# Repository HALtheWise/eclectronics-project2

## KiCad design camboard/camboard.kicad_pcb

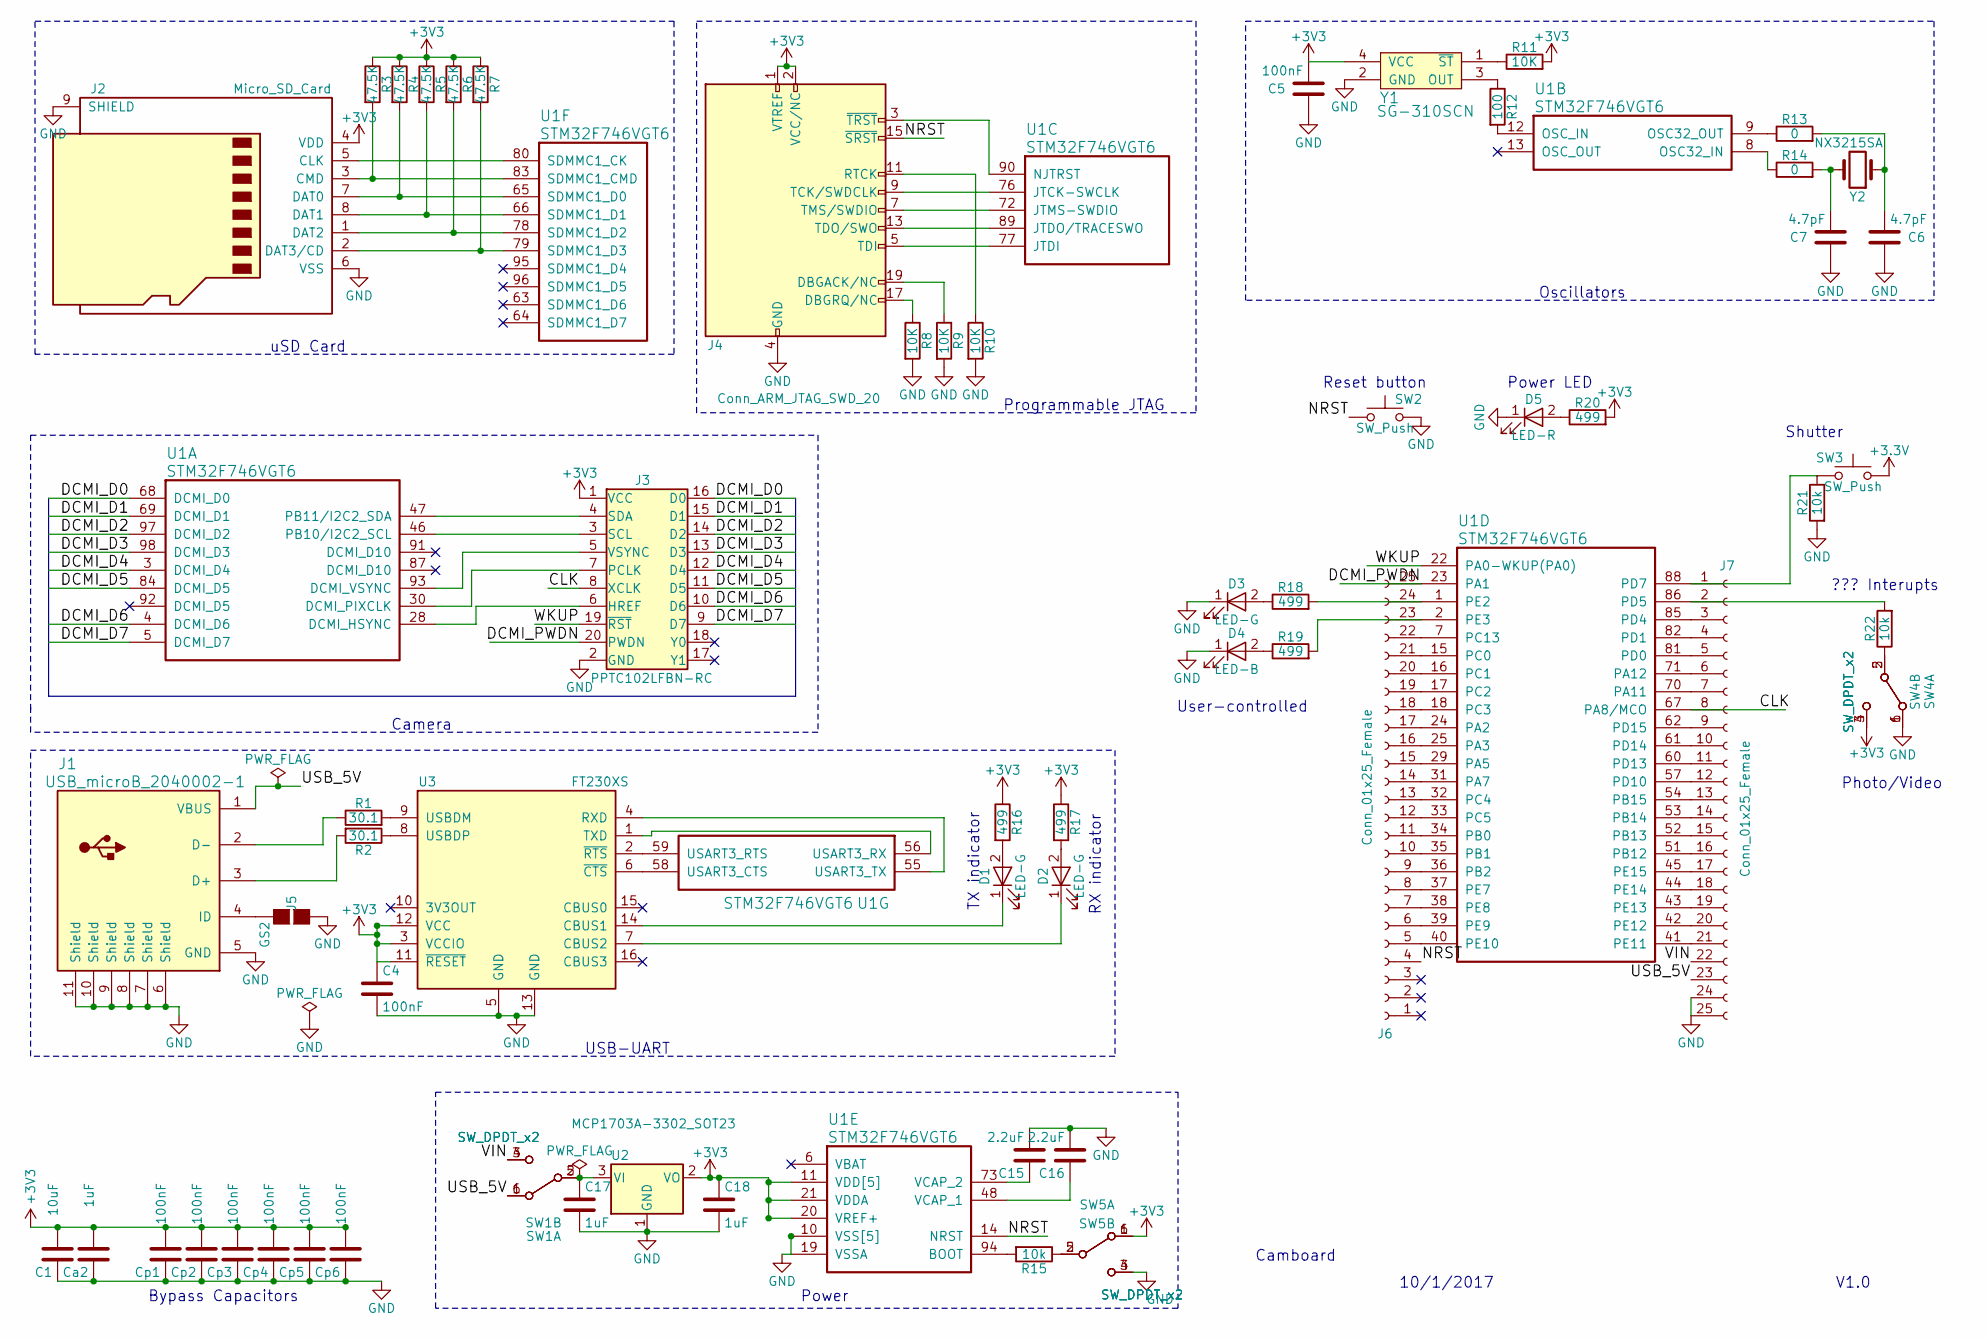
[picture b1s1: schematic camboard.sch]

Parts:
C1: 10uF; C_0805
C4, C5: 100nF; C_0603
C6, C7: 4.7pF; C_0603
C15, C16: 2.2uF; C_0805
C17, C18: 1uF; C_0603
Ca2: 1uF; C_0603
Cp1, Cp2, Cp3, Cp4, Cp5, Cp6: 100nF; C_0603
D1, D2, D3: LED-G; LED_0805
D4: LED-B; LED_0805
D5: LED-R; LED_0805
J1: USB_microB_2040002-1; USB_microB_2040002-1_alt
J2: Micro_SD_Card; 114-00841-68
J3: PPTC102LFBN-RC; Socket_Strip_Straight_2x10_Pitch2.54mm
J4: Conn_ARM_JTAG_SWD_20; Socket_Strip_Straight_2x10_Pitch2.54mm
J5: GS2
J6, J7: Conn_01x25_Female; Socket_Strip_Straight_1x25_Pitch2.54mm
R1, R2: 30.1; R_0603
R3, R4, R5, R6, R7: 47.5K; R_0603
R8, R9, R10, R11: 10K; R_0603
R12: 100; R_0603
R13, R14: 0; R_0603
R15, R21, R22: 10k; R_0603
R16, R17, R18, R19, R20: 499; R_0603
SW1, SW4, SW5: SW_DPDT_x2; JS202011SCQN
SW2, SW3: SW_Push; SW_SPST_B3U-1000P
U1: STM32F746VGT6; LQFP-100_14x14mm_Pitch0.5mm
U2: MCP1703A-3302_SOT23; SOT-23
U3: FT230XS; SSOP-16_3.9x4.9mm_Pitch0.635mm
Y1: SG-310SCN; Crystal_SMD_3225-4pin_3.2x2.5mm
Y2: NX3215SA; Crystal_SMD_3215-2pin_3.2x1.5mm

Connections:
/CLK: J3.8 (XCLK), J7.8, U1.67 (PA8/MCO)
/DCMI_D0: J3.16 (D0), U1.68 (DCMI_D0)
/DCMI_D1: J3.15 (D1), U1.69 (DCMI_D1)
/DCMI_D2: J3.14 (D2), U1.97 (DCMI_D2)
/DCMI_D3: J3.13 (D3), U1.98 (DCMI_D3)
/DCMI_D4: J3.12 (D4), U1.3 (DCMI_D4)
/DCMI_D5: J3.11 (D5), U1.84 (DCMI_D5)
/DCMI_D6: J3.10 (D6), U1.4 (DCMI_D6)
/DCMI_D7: J3.9 (D7), U1.5 (DCMI_D7)
/DCMI_PWDN: J3.20 (PWDN), J6.25, U1.23 (PA1)
/NRST: J4.15 (~SRST~), J6.4, SW2.1, U1.14 (NRST)
/USB_5V: J1.1 (VBUS), J7.23, SW1.1 (A), SW1.6 (A)
/VIN: J7.22, SW1.3 (C), SW1.4 (C)
/WKUP: J3.19 (~RST), U1.22 (PA0-WKUP(PA0))
GND: C1.1, C4.2, C5.1, C6.2, C7.1, C15.2, C16.2, C17.2, C18.2, Ca2.1, Cp1.1, Cp2.1, Cp3.1, Cp4.1, Cp5.1, Cp6.1, D3.1 (K), D4.1 (K), D5.1 (K), J1.5 (GND), J1.6 (Shield), J1.7 (Shield), J1.8 (Shield), J1.9 (Shield), J1.10 (Shield), J1.11 (Shield), J2.6 (VSS), J2.9 (SHIELD), J3.2 (GND), J4.4 (GND), J4.6 (GND), J4.8 (GND), J4.10 (GND), J4.12 (GND), J4.14 (GND), J4.16 (GND), J4.18 (GND), J4.20 (GND), J5.1 (G1), J7.24, J7.25, R8.2, R9.2, R10.2, R21.2, SW2.2, SW4.1 (A), SW4.6 (A), SW5.3 (C), SW5.4 (C), U1.10 (VSS[5]), U1.19 (VSSA), U1.26 (VSS[5]), U1.49 (VSS[5]), U1.74 (VSS[5]), U1.99 (VSS[5]), U2.1 (GND), U3.5 (GND), U3.13 (GND), Y1.2 (GND)
unnamed: C6.1, R13.2, Y2.1
unnamed: C7.2, R14.2, Y2.2
unnamed: C15.1, U1.73 (VCAP_2)
unnamed: C16.1, U1.48 (VCAP_1)
unnamed: C17.1, SW1.2 (B), SW1.5 (B), U2.3 (VI)
unnamed: D1.1 (K), U3.14 (CBUS1)
unnamed: D1.2 (A), R16.2
unnamed: D2.1 (K), U3.7 (CBUS2)
unnamed: D2.2 (A), R17.2
unnamed: D3.2 (A), R18.1
unnamed: D4.2 (A), R19.1
unnamed: D5.2 (A), R20.1
unnamed: J1.2 (D-), R1.1
unnamed: J1.3 (D+), R2.2
unnamed: J1.4 (ID), J5.2 (G2)
unnamed: J2.1 (DAT2), R6.2, U1.78 (SDMMC1_D2)
unnamed: J2.2 (DAT3/CD), R7.2, U1.79 (SDMMC1_D3)
unnamed: J2.3 (CMD), R3.2, U1.83 (SDMMC1_CMD)
unnamed: J2.5 (CLK), U1.80 (SDMMC1_CK)
unnamed: J2.7 (DAT0), R4.2, U1.65 (SDMMC1_D0)
unnamed: J2.8 (DAT1), R5.2, U1.66 (SDMMC1_D1)
unnamed: J3.3 (SCL), U1.46 (PB10/I2C2_SCL)
unnamed: J3.4 (SDA), U1.47 (PB11/I2C2_SDA)
unnamed: J3.5 (VSYNC), U1.93 (DCMI_VSYNC)
unnamed: J3.6 (HREF), U1.28 (DCMI_HSYNC)
unnamed: J3.7 (PCLK), U1.30 (DCMI_PIXCLK)
unnamed: J4.3 (~TRST~), U1.90 (NJTRST)
unnamed: J4.5 (TDI), U1.77 (JTDI)
unnamed: J4.7 (TMS/SWDIO), U1.72 (JTMS-SWDIO)
unnamed: J4.9 (TCK/SWDCLK), U1.76 (JTCK-SWCLK)
unnamed: J4.11 (RTCK), R10.1
unnamed: J4.13 (TDO/SWO), U1.89 (JTDO/TRACESWO)
unnamed: J4.17 (DBGRQ/NC), R8.1
unnamed: J4.19 (DBGACK/NC), R9.1
unnamed: J6.5, U1.40 (PE10)
unnamed: J6.6, U1.39 (PE9)
unnamed: J6.7, U1.38 (PE8)
unnamed: J6.8, U1.37 (PE7)
unnamed: J6.9, U1.36 (PB2)
unnamed: J6.10, U1.35 (PB1)
unnamed: J6.11, U1.34 (PB0)
unnamed: J6.12, U1.33 (PC5)
unnamed: J6.13, U1.32 (PC4)
unnamed: J6.14, U1.31 (PA7)
unnamed: J6.15, U1.29 (PA5)
unnamed: J6.16, U1.25 (PA3)
unnamed: J6.17, U1.24 (PA2)
unnamed: J6.18, U1.18 (PC3)
unnamed: J6.19, U1.17 (PC2)
unnamed: J6.20, U1.16 (PC1)
unnamed: J6.21, U1.15 (PC0)
unnamed: J6.22, U1.7 (PC13)
unnamed: J6.23, R19.2, U1.2 (PE3)
unnamed: J6.24, R18.2, U1.1 (PE2)
unnamed: J7.1, R21.1, SW3.2, U1.88 (PD7)
unnamed: J7.2, R22.2, U1.86 (PD5)
unnamed: J7.3, U1.85 (PD4)
unnamed: J7.4, U1.82 (PD1)
unnamed: J7.5, U1.81 (PD0)
unnamed: J7.6, U1.71 (PA12)
unnamed: J7.7, U1.70 (PA11)
unnamed: J7.9, U1.62 (PD15)
unnamed: J7.10, U1.61 (PD14)
unnamed: J7.11, U1.60 (PD13)
unnamed: J7.12, U1.57 (PD10)
unnamed: J7.13, U1.54 (PB15)
unnamed: J7.14, U1.53 (PB14)
unnamed: J7.15, U1.52 (PB13)
unnamed: J7.16, U1.51 (PB12)
unnamed: J7.17, U1.45 (PE15)
unnamed: J7.18, U1.44 (PE14)
unnamed: J7.19, U1.43 (PE13)
unnamed: J7.20, U1.42 (PE12)
unnamed: J7.21, U1.41 (PE11)
unnamed: R1.2, U3.9 (USBDM)
unnamed: R2.1, U3.8 (USBDP)
unnamed: R11.1, Y1.1 (~ST)
unnamed: R12.1, Y1.3 (OUT)
unnamed: R12.2, U1.12 (OSC_IN)
unnamed: R13.1, U1.9 (OSC32_OUT)
unnamed: R14.1, U1.8 (OSC32_IN)
unnamed: R15.1, SW5.2 (B), SW5.5 (B)
unnamed: R15.2, U1.94 (BOOT)
unnamed: R22.1, SW4.2 (B), SW4.5 (B)
unnamed: U1.55 (USART3_TX), U3.4 (RXD)
unnamed: U1.56 (USART3_RX), U3.1 (TXD)
unnamed: U1.58 (USART3_CTS), U3.6 (~CTS)
unnamed: U1.59 (USART3_RTS), U3.2 (~RTS)

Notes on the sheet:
Oscillators
USB-UART
uSD Card
Camera
Programmable JTAG
Power
RX indicator
TX indicator
Photo/Video
Shutter
Power LED
Reset button
User-controlled
Bypass Capacitors
Camboard
10/1/2017
V1.0
??? Interupts

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
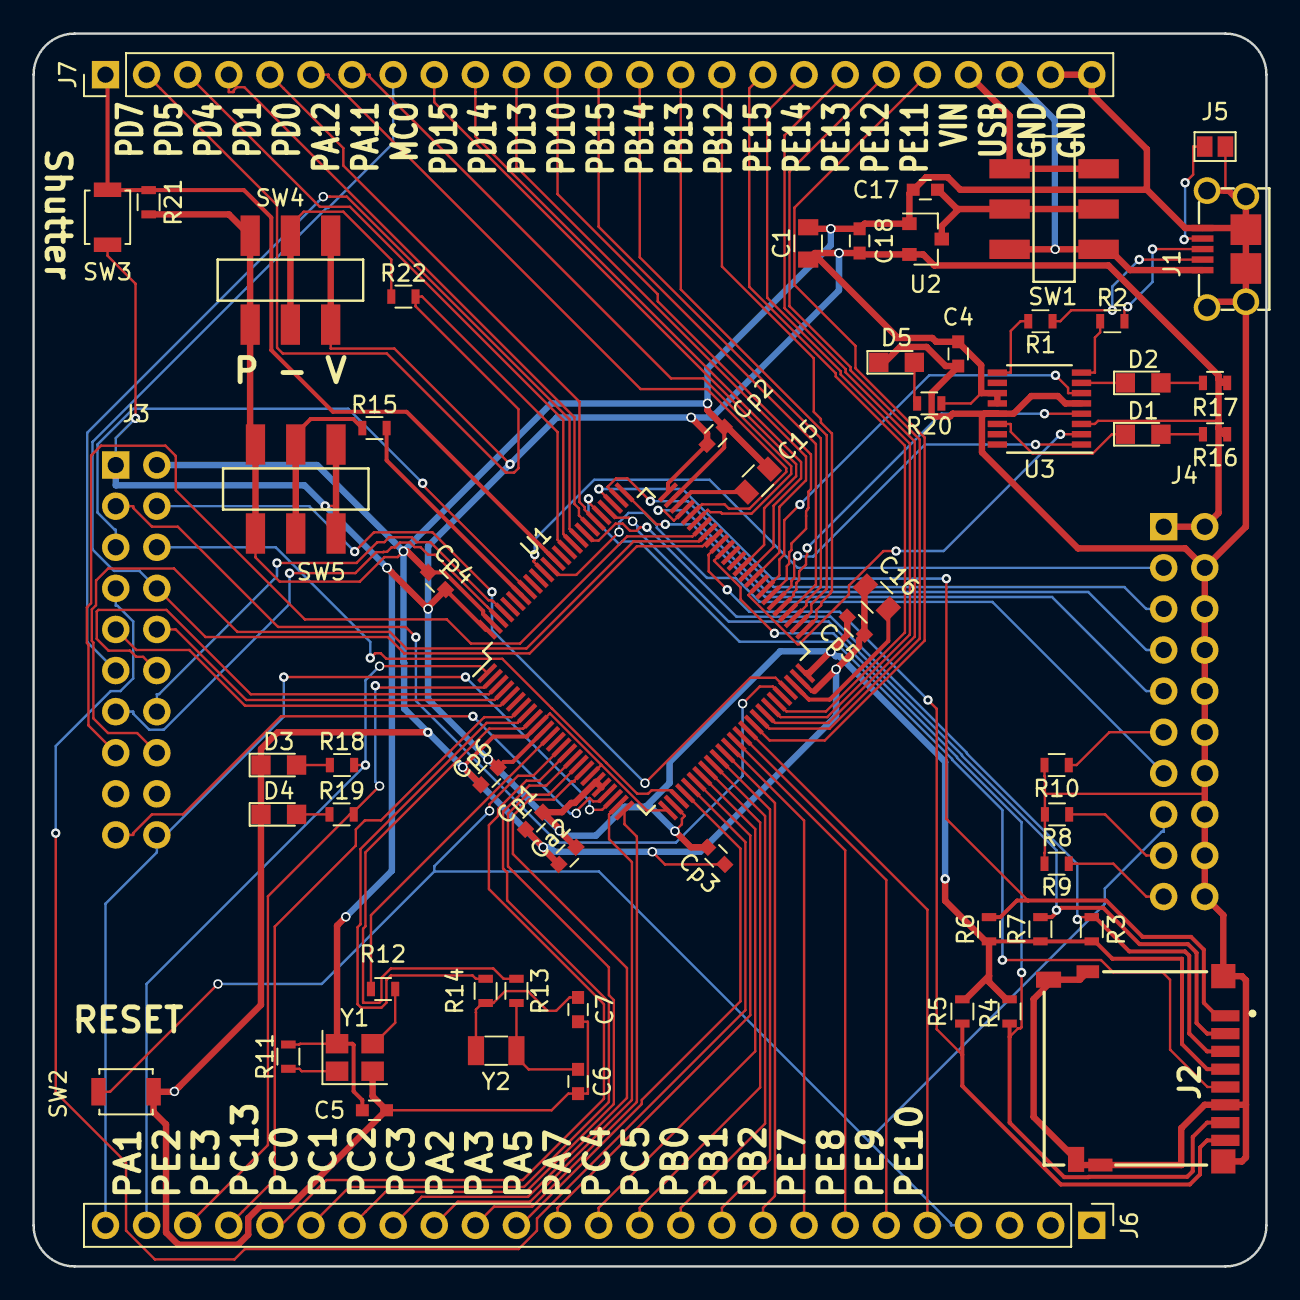
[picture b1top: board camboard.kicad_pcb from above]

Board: 2 copper layers, 76.2 x 76.2 mm, 60 parts (0 on the bottom side), 104 nets.

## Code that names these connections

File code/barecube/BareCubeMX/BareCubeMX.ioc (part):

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Mcu.Name=STM32F746VGTx
Mcu.Package=LQFP100
Mcu.UserName=STM32F746VGTx
PA0/WKUP.GPIOParameters=PinState,GPIO_PuPd,GPIO_Label
PA0/WKUP.GPIO_Label=CAM_RESET
PA0/WKUP.GPIO_PuPd=GPIO_PULLUP
PA0/WKUP.PinState=GPIO_PIN_SET
PA0/WKUP.Signal=GPIO_Output
PA10.Mode=Slave_8_bits_External_Synchro
PA10.Signal=DCMI_D1
PA4.Mode=Slave_8_bits_External_Synchro
PA4.Signal=DCMI_HSYNC
PA6.Mode=Slave_8_bits_External_Synchro
PA6.Signal=DCMI_PIXCLK
PA9.Mode=Slave_8_bits_External_Synchro
PA9.Signal=DCMI_D0
PB10.Mode=I2C
PB10.Signal=I2C2_SCL
PB11.Mode=I2C
PB11.Signal=I2C2_SDA
PB7.Mode=Slave_8_bits_External_Synchro
PB7.Signal=DCMI_VSYNC
PD3.Mode=Slave_8_bits_External_Synchro
PD3.Signal=DCMI_D5
PD5.GPIOParameters=GPIO_Label
PD5.GPIO_Label=PVSWITCH
PD5.Signal=GPIO_Input
PD7.GPIOParameters=GPIO_Label
PD7.GPIO_Label=SHUTTER
PD7.Signal=GPIO_Input
PD8.Mode=Asynchronous
PD8.Signal=USART3_TX
PD9.Mode=Asynchronous
PD9.Signal=USART3_RX
PE0.Mode=Slave_8_bits_External_Synchro
PE0.Signal=DCMI_D2
PE1.Mode=Slave_8_bits_External_Synchro
PE1.Signal=DCMI_D3
PE2.GPIOParameters=GPIO_Label
PE2.GPIO_Label=LEDG
PE2.Signal=GPIO_Output
PE3.GPIOParameters=PinState,GPIO_Label
PE3.GPIO_Label=LEDR
PE3.PinState=GPIO_PIN_SET
PE3.Signal=GPIO_Output
PE4.Mode=Slave_8_bits_External_Synchro
PE4.Signal=DCMI_D4
PE5.Mode=Slave_8_bits_External_Synchro
PE5.Signal=DCMI_D6
PE6.Mode=Slave_8_bits_External_Synchro
PE6.Signal=DCMI_D7
RCC.HSE_VALUE=25000000
board=BareCubeMX

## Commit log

2017-09-23 Added gitignore for kicad
2017-09-25 Created kicad project
2017-09-25 Added library file
2017-09-25 Loaded library
2017-09-25 Assigned pin numbers for DCMI camer interface
2017-09-25 Minor modifications to library
2017-09-26 Final changes after class for STM32 part
2017-09-27 Added v2 of stm32 chip, made using kipart
2017-09-27 Added processor to schematic
2017-09-27 Added camera connector library
2017-09-27 Added footprint for processor
2017-09-27 Added JTAG port schematic
2017-09-27 Moved components into proper directory
2017-09-27 added oscillators
2017-09-27 Added components
2017-09-27 Added more components and fixed SD card pinout
2017-09-27 fixed wrong library reference and added power select
2017-09-27 Added button
2017-09-27 more connections
2017-09-27 added microSD connections, camera very ambiguous
2017-09-28 added JTAG Connection
2017-09-28 added usb-uart
2017-09-28 some peripherals are done
2017-09-28 added some labels
2017-09-28 Added i2c pins to camera block
2017-09-28 Fixed camera connections
2017-09-28 Added bypass caps
2017-09-28 Fixed some issues
2017-09-29 added USB micro
2017-09-29 modified resistor values, etc.
2017-09-29 Added headers
2017-09-29 Added longer headers
2017-09-29 Added user-controlled buttons and LED's
2017-10-01 modifying layout to maximize spacing between logical units, some footprint association. set LED resistance to 100 ohms for now.
2017-10-01 Adjusted resistor values and stuff
2017-10-03 In-class 10/2
2017-10-05 Added boxes
2017-10-05 Schematic review
2017-10-06 updated connectorsx25 and associated most footprints
2017-10-06 added DPDT Switch Footprints
2017-10-06 fixed switch annotation
2017-10-06 Fixed some notes from design review
2017-10-06 Fixed oscillator symbol
2017-10-06 Finished schematic
2017-10-07 Fixed some footprints
2017-10-07 2x1->1x2
2017-10-07 updated switch schematic
2017-10-07 properly updated switch
2017-10-07 Placed components (for now)
2017-10-07 remove cp7
2017-10-07 Finished(ish) placing components
2017-10-07 fixed jtag
2017-10-07 Autorouted (attempt 1)
2017-10-07 Fixed some stupid routing choices
2017-10-07 Manual pre-routing of power
2017-10-07 The ladybug is happy
2017-10-07 Added jar
2017-10-07 better layout?
2017-10-07 auto routing attempt 3 - main processor 45 degree
2017-10-11 Moved SD card and processor
2017-10-11 Kept moving parts
2017-10-11 More power traces and cam clock
2017-10-11 Moved some more components
2017-10-11 Pre-autoroute
2017-10-11 autoroute
2017-10-11 Final autorouting
2017-10-12 updated pcb
2017-10-12 Fixed some silly traces
2017-10-12 More changes
2017-10-12 report-version
2017-10-13 beautifying
2017-10-13 fixing image ref in README
2017-10-13 fix dumb typo
2017-11-29 Started working on code
2017-11-29 v2 code started
2017-11-30 Finished work 11/29
2017-12-09 Working GPIO input and output
2017-12-09 Working USART
2017-12-15 Added I2C support
2017-12-15 Began working with I2C
2017-12-15 Added reset pin for camera
